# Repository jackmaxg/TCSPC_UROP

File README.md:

# TCSPC_UROP
Time Correlated Single Photon Counting Module

This is an open source project to develop a ~10 picosecond precision timing module, for time correlating pulses output by an avalanche photodiode quench circuit.

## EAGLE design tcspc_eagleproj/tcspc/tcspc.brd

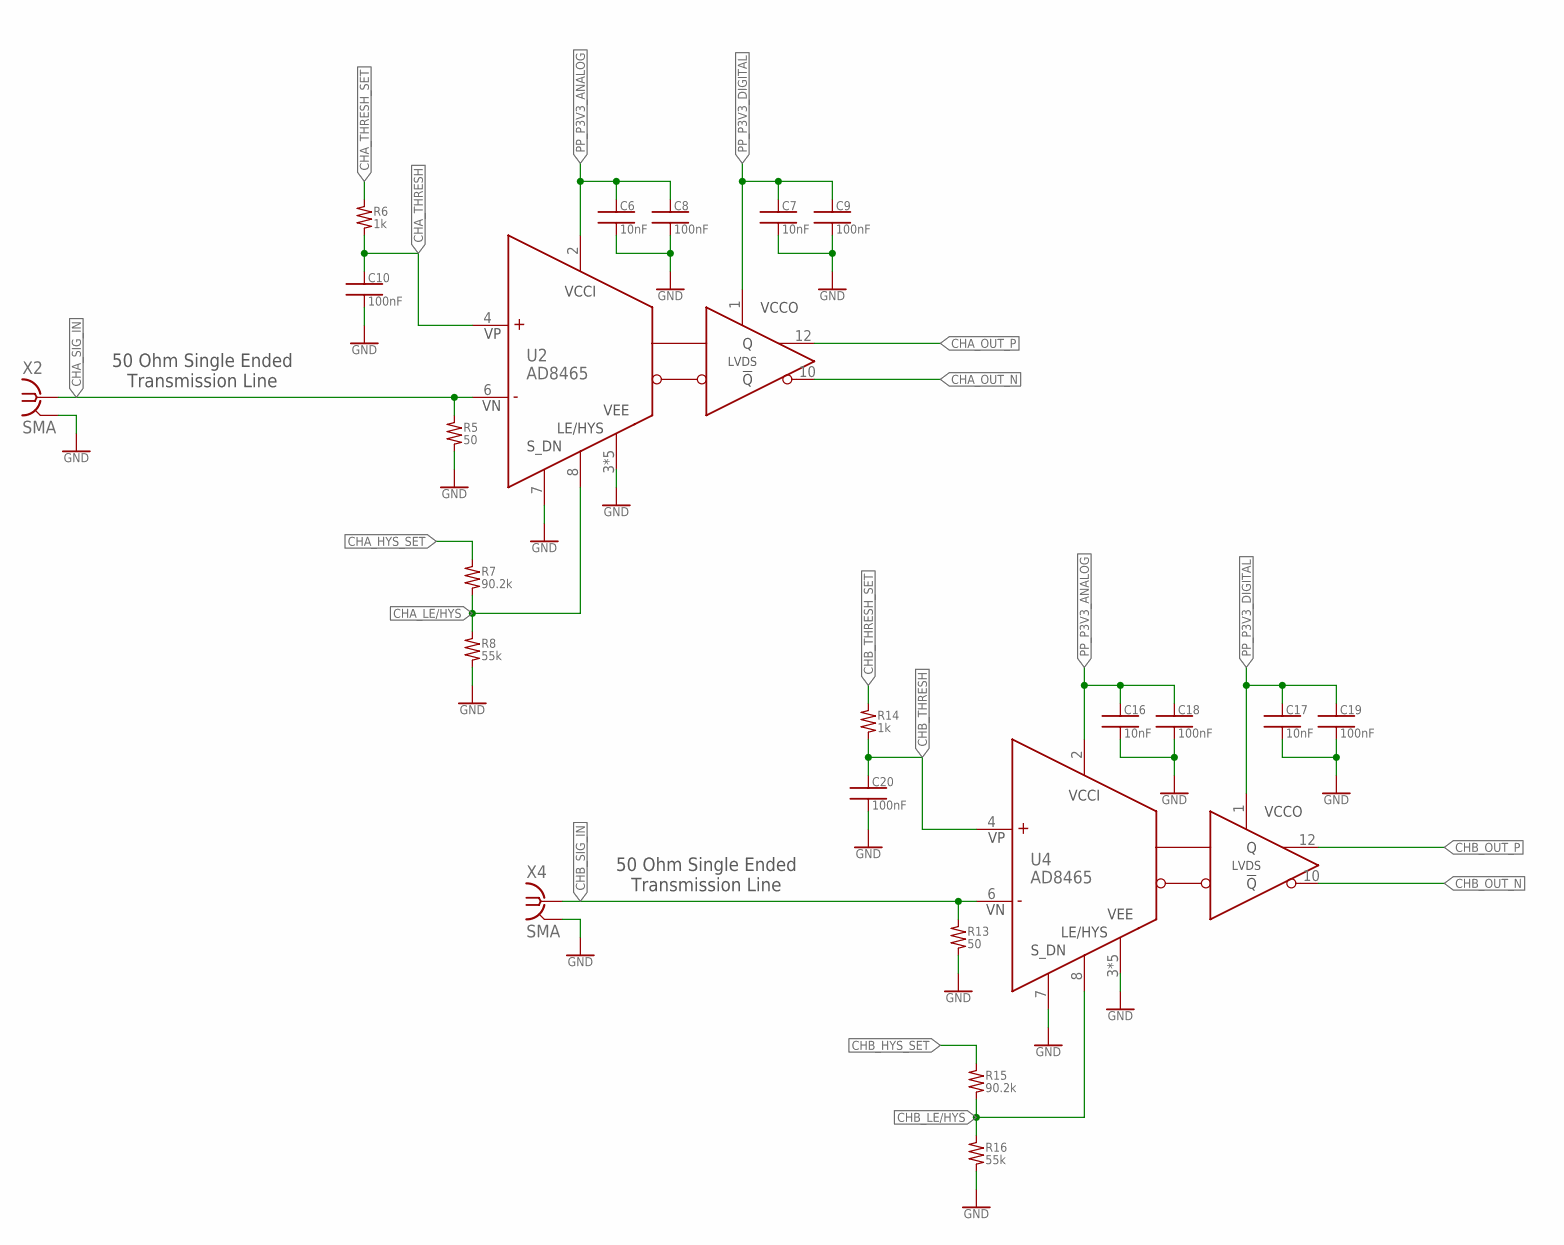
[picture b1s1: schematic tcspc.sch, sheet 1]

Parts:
C6, C7, C16, C17: 10nF; 0402
C8, C9, C10, C18, C19, C20: 100nF; 0402
R5, R13: 50; 0402
R6, R14: 1k; 0402
R7, R15: 90.2k; 0402
R8, R16: 55k; 0402
U2, U4: AD8465; LFCSP-12
X2, X4: SMA; J502-ND-142-0701-881/886

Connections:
CHA_HYS_SET: R7.1
CHA_LE/HYS: R7.2, R8.1, U2.8 (LE/HYS)
CHA_OUT_N: U2.10 (!Q)
CHA_OUT_P: U2.12 (Q)
CHA_SIG_IN: R5.1, U2.6 (VN), X2.1
CHA_THRESH: C10.1, R6.2, U2.4 (VP)
CHA_THRESH_SET: R6.1
CHB_HYS_SET: R15.1
CHB_LE/HYS: R15.2, R16.1, U4.8 (LE/HYS)
CHB_OUT_N: U4.10 (!Q)
CHB_OUT_P: U4.12 (Q)
CHB_SIG_IN: R13.1, U4.6 (VN), X4.1
CHB_THRESH: C20.1, R14.2, U4.4 (VP)
CHB_THRESH_SET: R14.1
GND: C6.2, C7.2, C8.2, C9.2, C10.2, C16.2, C17.2, C18.2, C19.2, C20.2, R5.2, R8.2, R13.2, R16.2, U2.3 (VEE), U2.5 (VEE), U2.7 (SDN), U2.9 (VEE), U2.11 (VEE), U2.EPAD (VEE), U4.3 (VEE), U4.5 (VEE), U4.7 (SDN), U4.9 (VEE), U4.11 (VEE), U4.EPAD (VEE), X2.G@1 (GND), X2.G@2 (GND), X2.G@3 (GND), X2.G@4 (GND), X4.G@1 (GND), X4.G@2 (GND), X4.G@3 (GND), X4.G@4 (GND); also elsewhere on the board
PP_P3V3_ANALOG: C6.1, C8.1, C16.1, C18.1, U2.2 (VCCI), U4.2 (VCCI); also elsewhere on the board
PP_P3V3_DIGITAL: C7.1, C9.1, C17.1, C19.1, U2.1 (VCCO), U4.1 (VCCO); also elsewhere on the board

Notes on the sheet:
50 Ohm Single Ended Transmission Line

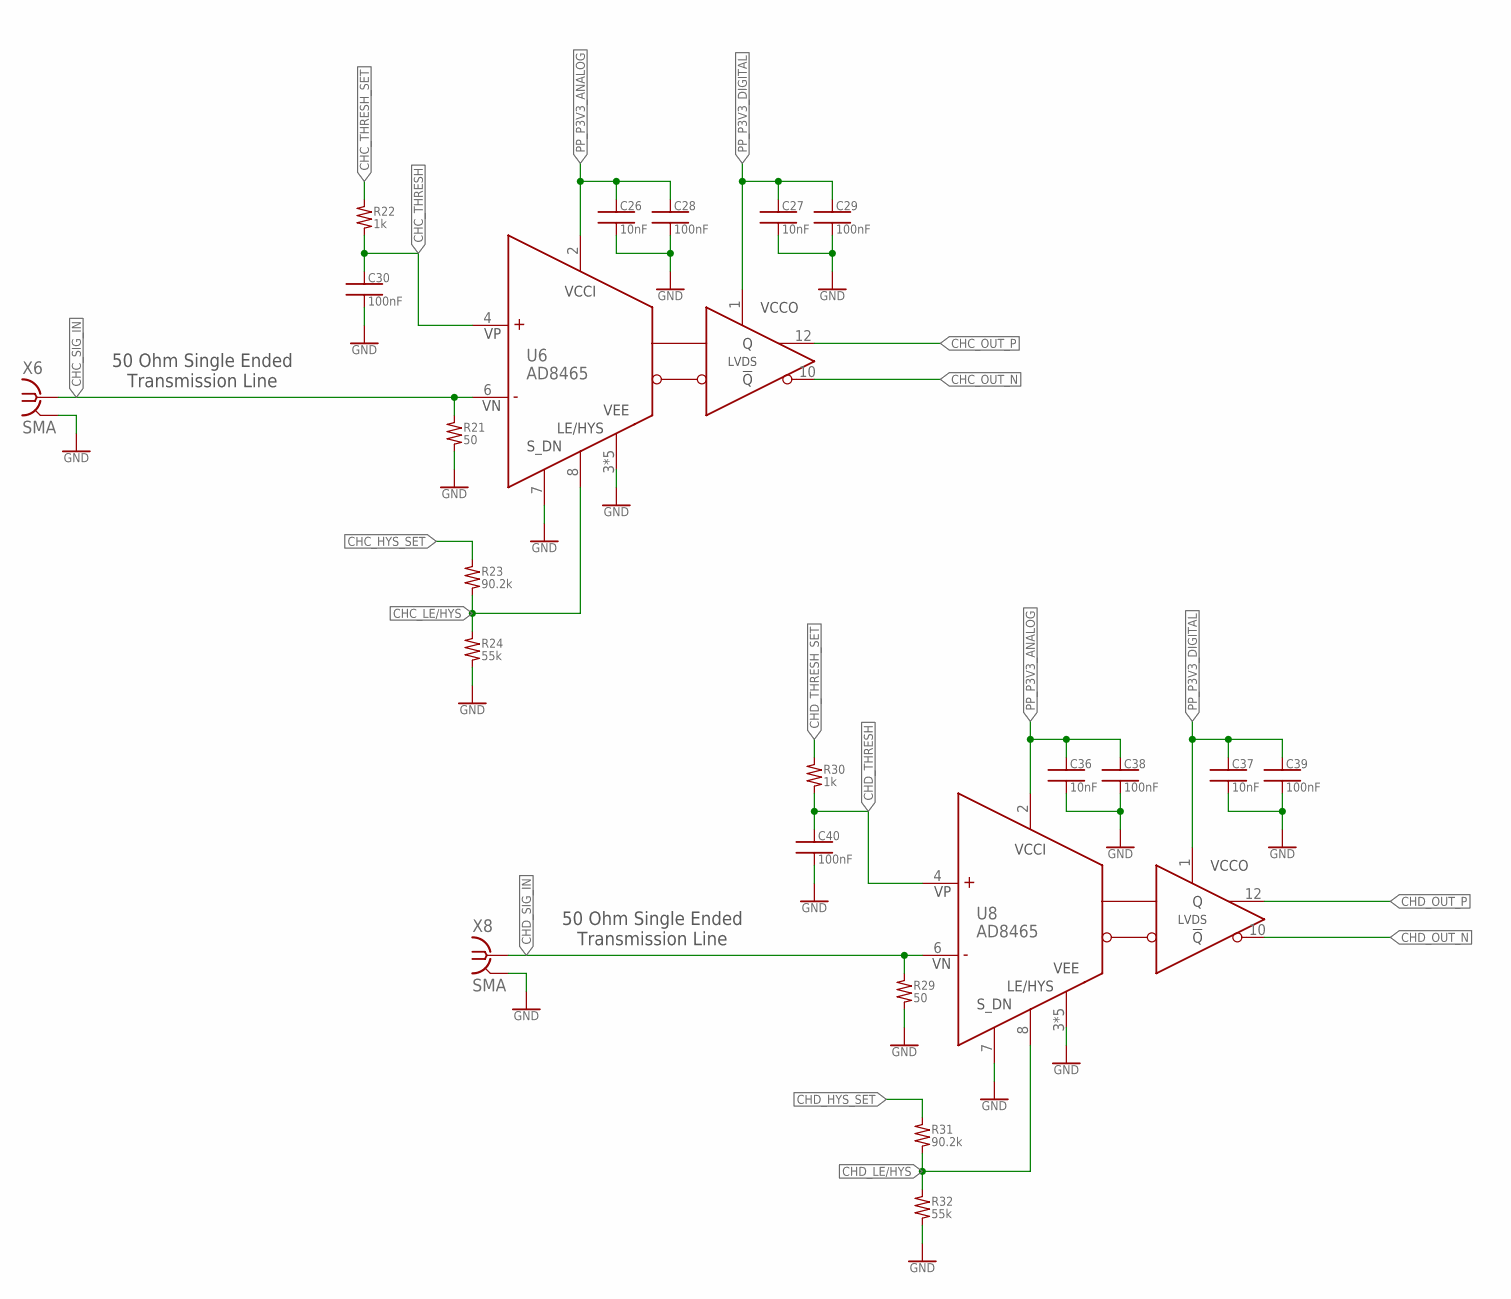
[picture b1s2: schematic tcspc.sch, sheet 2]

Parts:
C26, C27, C36, C37: 10nF; 0402
C28, C29, C30, C38, C39, C40: 100nF; 0402
R21, R29: 50; 0402
R22, R30: 1k; 0402
R23, R31: 90.2k; 0402
R24, R32: 55k; 0402
U6, U8: AD8465; LFCSP-12
X6, X8: SMA; J502-ND-142-0701-881/886

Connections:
CHC_HYS_SET: R23.1
CHC_LE/HYS: R23.2, R24.1, U6.8 (LE/HYS)
CHC_OUT_N: U6.10 (!Q)
CHC_OUT_P: U6.12 (Q)
CHC_SIG_IN: R21.1, U6.6 (VN), X6.1
CHC_THRESH: C30.1, R22.2, U6.4 (VP)
CHC_THRESH_SET: R22.1
CHD_HYS_SET: R31.1
CHD_LE/HYS: R31.2, R32.1, U8.8 (LE/HYS)
CHD_OUT_N: U8.10 (!Q)
CHD_OUT_P: U8.12 (Q)
CHD_SIG_IN: R29.1, U8.6 (VN), X8.1
CHD_THRESH: C40.1, R30.2, U8.4 (VP)
CHD_THRESH_SET: R30.1
GND: C26.2, C27.2, C28.2, C29.2, C30.2, C36.2, C37.2, C38.2, C39.2, C40.2, R21.2, R24.2, R29.2, R32.2, U6.3 (VEE), U6.5 (VEE), U6.7 (SDN), U6.9 (VEE), U6.11 (VEE), U6.EPAD (VEE), U8.3 (VEE), U8.5 (VEE), U8.7 (SDN), U8.9 (VEE), U8.11 (VEE), U8.EPAD (VEE), X6.G@1 (GND), X6.G@2 (GND), X6.G@3 (GND), X6.G@4 (GND), X8.G@1 (GND), X8.G@2 (GND), X8.G@3 (GND), X8.G@4 (GND); also elsewhere on the board
PP_P3V3_ANALOG: C26.1, C28.1, C36.1, C38.1, U6.2 (VCCI), U8.2 (VCCI); also elsewhere on the board
PP_P3V3_DIGITAL: C27.1, C29.1, C37.1, C39.1, U6.1 (VCCO), U8.1 (VCCO); also elsewhere on the board

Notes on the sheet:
50 Ohm Single Ended Transmission Line

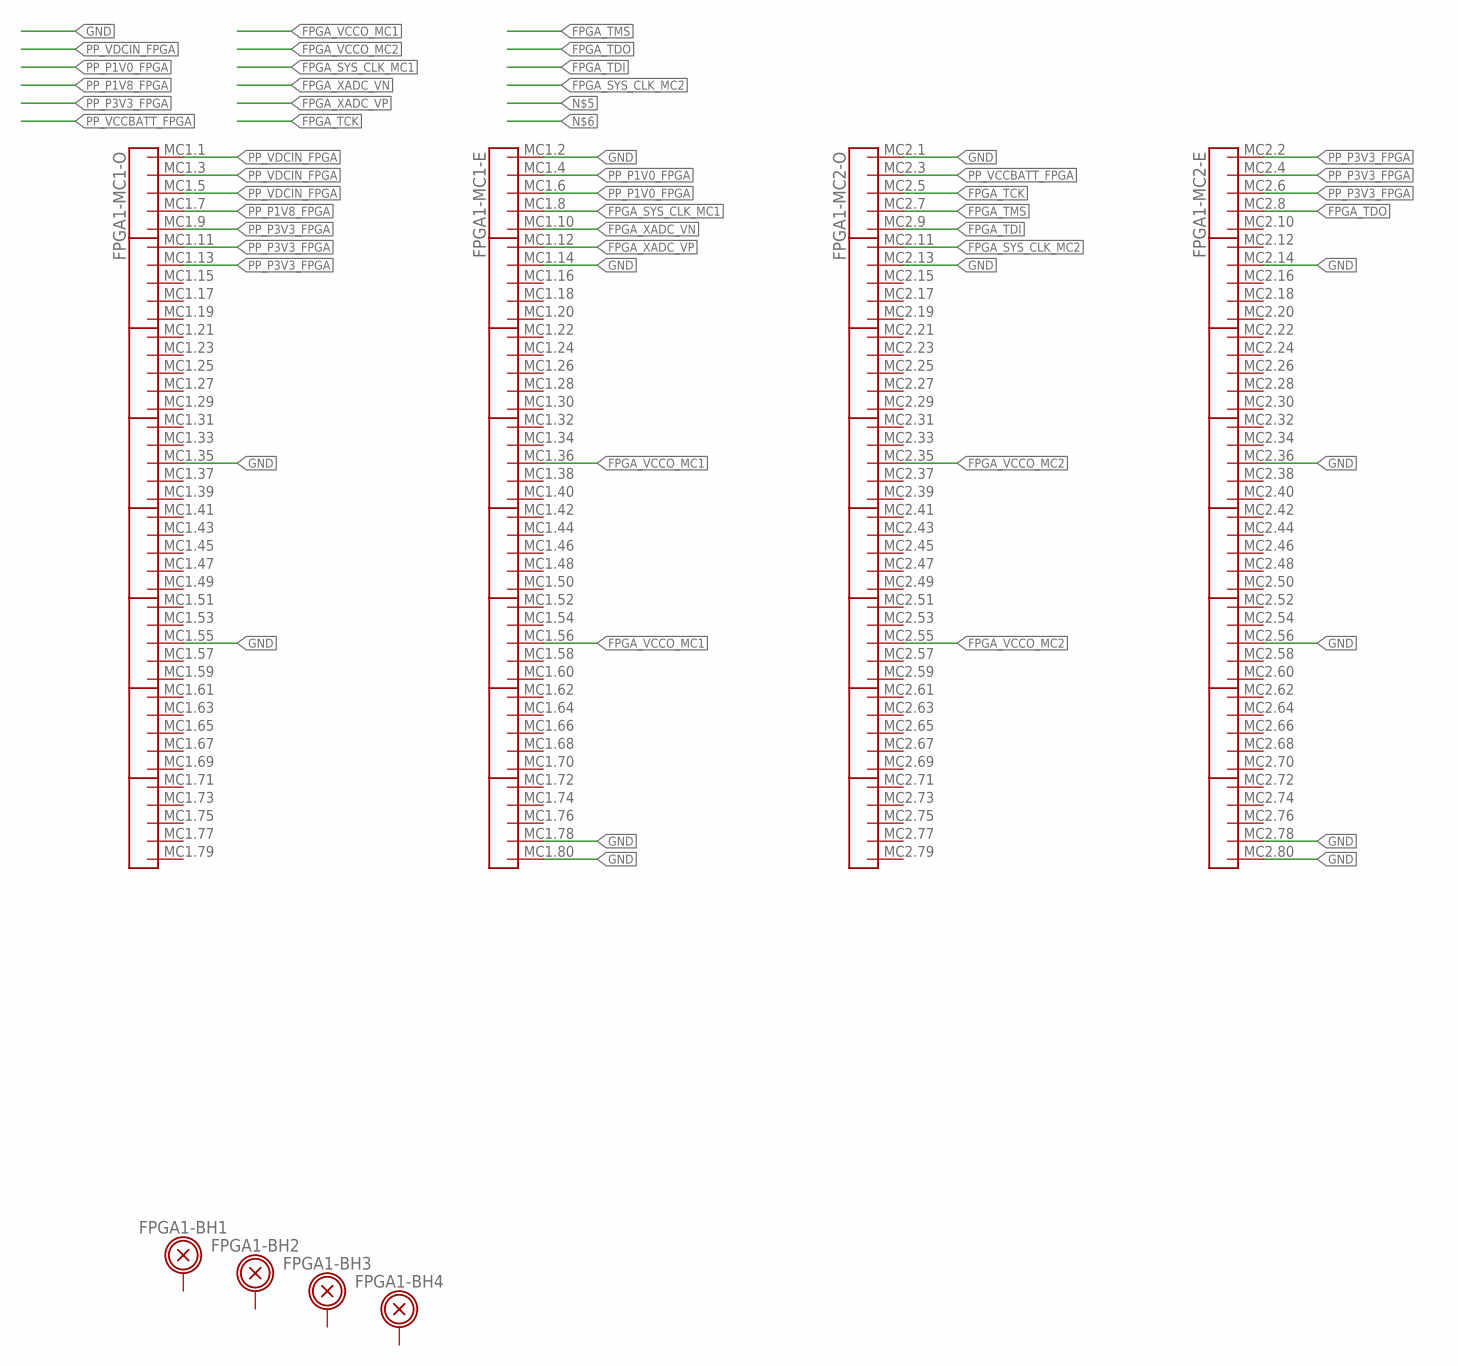
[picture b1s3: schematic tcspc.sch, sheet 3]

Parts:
FPGA1: XEM7310

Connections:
FPGA_SYS_CLK_MC1: FPGA1.MC1.8 (P4)
FPGA_SYS_CLK_MC2: FPGA1.MC2.11 (P6)
FPGA_TCK: FPGA1.MC2.5 (P3)
FPGA_TDI: FPGA1.MC2.9 (P5)
FPGA_TDO: FPGA1.MC2.8 (P4)
FPGA_TMS: FPGA1.MC2.7 (P4)
FPGA_VCCO_MC1: FPGA1.MC1.36 (P18), FPGA1.MC1.56 (P28)
FPGA_VCCO_MC2: FPGA1.MC2.35 (P18), FPGA1.MC2.55 (P28)
FPGA_XADC_VN: FPGA1.MC1.10 (P5)
FPGA_XADC_VP: FPGA1.MC1.12 (P6)
GND: FPGA1.MC1.2 (P1), FPGA1.MC1.14 (P7), FPGA1.MC1.35 (P18), FPGA1.MC1.55 (P28), FPGA1.MC1.78 (P39), FPGA1.MC1.80 (P40), FPGA1.MC2.1 (P1), FPGA1.MC2.13 (P7), FPGA1.MC2.14 (P7), FPGA1.MC2.36 (P18), FPGA1.MC2.56 (P28), FPGA1.MC2.78 (P39), FPGA1.MC2.80 (P40); also elsewhere on the board
PP_P1V0_FPGA: FPGA1.MC1.4 (P2), FPGA1.MC1.6 (P3)
PP_P1V8_FPGA: FPGA1.MC1.7 (P4)
PP_P3V3_FPGA: FPGA1.MC1.9 (P5), FPGA1.MC1.11 (P6), FPGA1.MC1.13 (P7), FPGA1.MC2.2 (P1), FPGA1.MC2.4 (P2), FPGA1.MC2.6 (P3)
PP_VCCBATT_FPGA: FPGA1.MC2.3 (P2)
PP_VDCIN_FPGA: FPGA1.MC1.1 (P1), FPGA1.MC1.3 (P2), FPGA1.MC1.5 (P3)

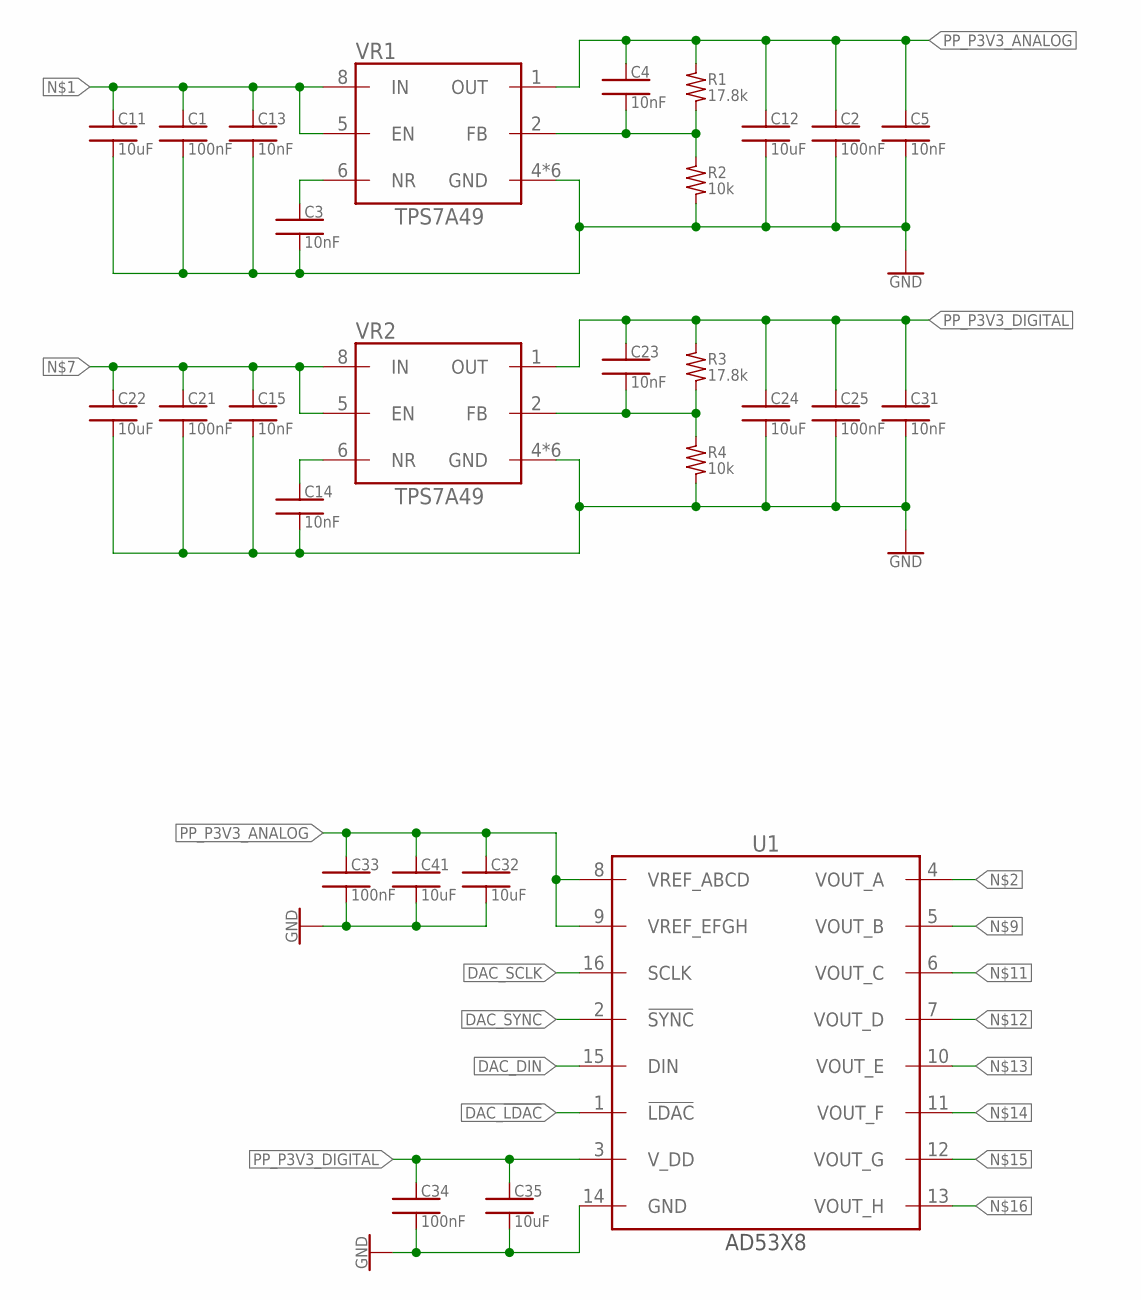
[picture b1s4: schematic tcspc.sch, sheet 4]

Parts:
C1, C2, C21, C25, C33, C34: 100nF; 0402
C3, C4, C5, C13, C14, C15, C23, C31: 10nF; 0402
C11, C12, C22, C24: 10uF; 0603
C32, C35, C41: 10uF; 0402
R1, R3: 17.8k; 0402
R2, R4: 10k; 0402
U1: AD53X8; TSSOP-16
VR1, VR2: TPS7A49; VSON

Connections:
DAC_!LDAC!: U1.1 (!LDAC)
DAC_!SYNC!: U1.2 (!SYNC)
DAC_DIN: U1.15 (DIN)
DAC_SCLK: U1.16 (SCLK)
GND: C1.2, C2.2, C3.2, C5.2, C11.2, C12.2, C13.2, C14.2, C15.2, C21.2, C22.2, C24.2, C25.2, C31.2, C32.2, C33.2, C34.2, C35.2, C41.2, R2.2, R4.2, U1.14 (GND), VR1.4 (GND), VR1.TP (GND), VR1.TP_A (GND), VR1.TP_B (GND), VR1.TP_C (GND), VR1.TP_D (GND), VR2.4 (GND), VR2.TP (GND), VR2.TP_A (GND), VR2.TP_B (GND), VR2.TP_C (GND), VR2.TP_D (GND); also elsewhere on the board
unnamed: C1.1, C11.1, C13.1, VR1.5 (EN), VR1.8 (IN)
unnamed: C4.2, R1.2, R2.1, VR1.2 (FB)
unnamed: C3.1, VR1.6 (NR)
unnamed: C15.1, C21.1, C22.1, VR2.5 (EN), VR2.8 (IN)
unnamed: C14.1, VR2.6 (NR)
unnamed: C23.2, R3.2, R4.1, VR2.2 (FB)
PP_P3V3_ANALOG: C2.1, C4.1, C5.1, C12.1, C32.1, C33.1, C41.1, R1.1, U1.8 (VREF_ABCD), U1.9 (VREF_EFGH), VR1.1 (OUT); also elsewhere on the board
PP_P3V3_DIGITAL: C23.1, C24.1, C25.1, C31.1, C34.1, C35.1, R3.1, U1.3 (V_DD), VR2.1 (OUT); also elsewhere on the board

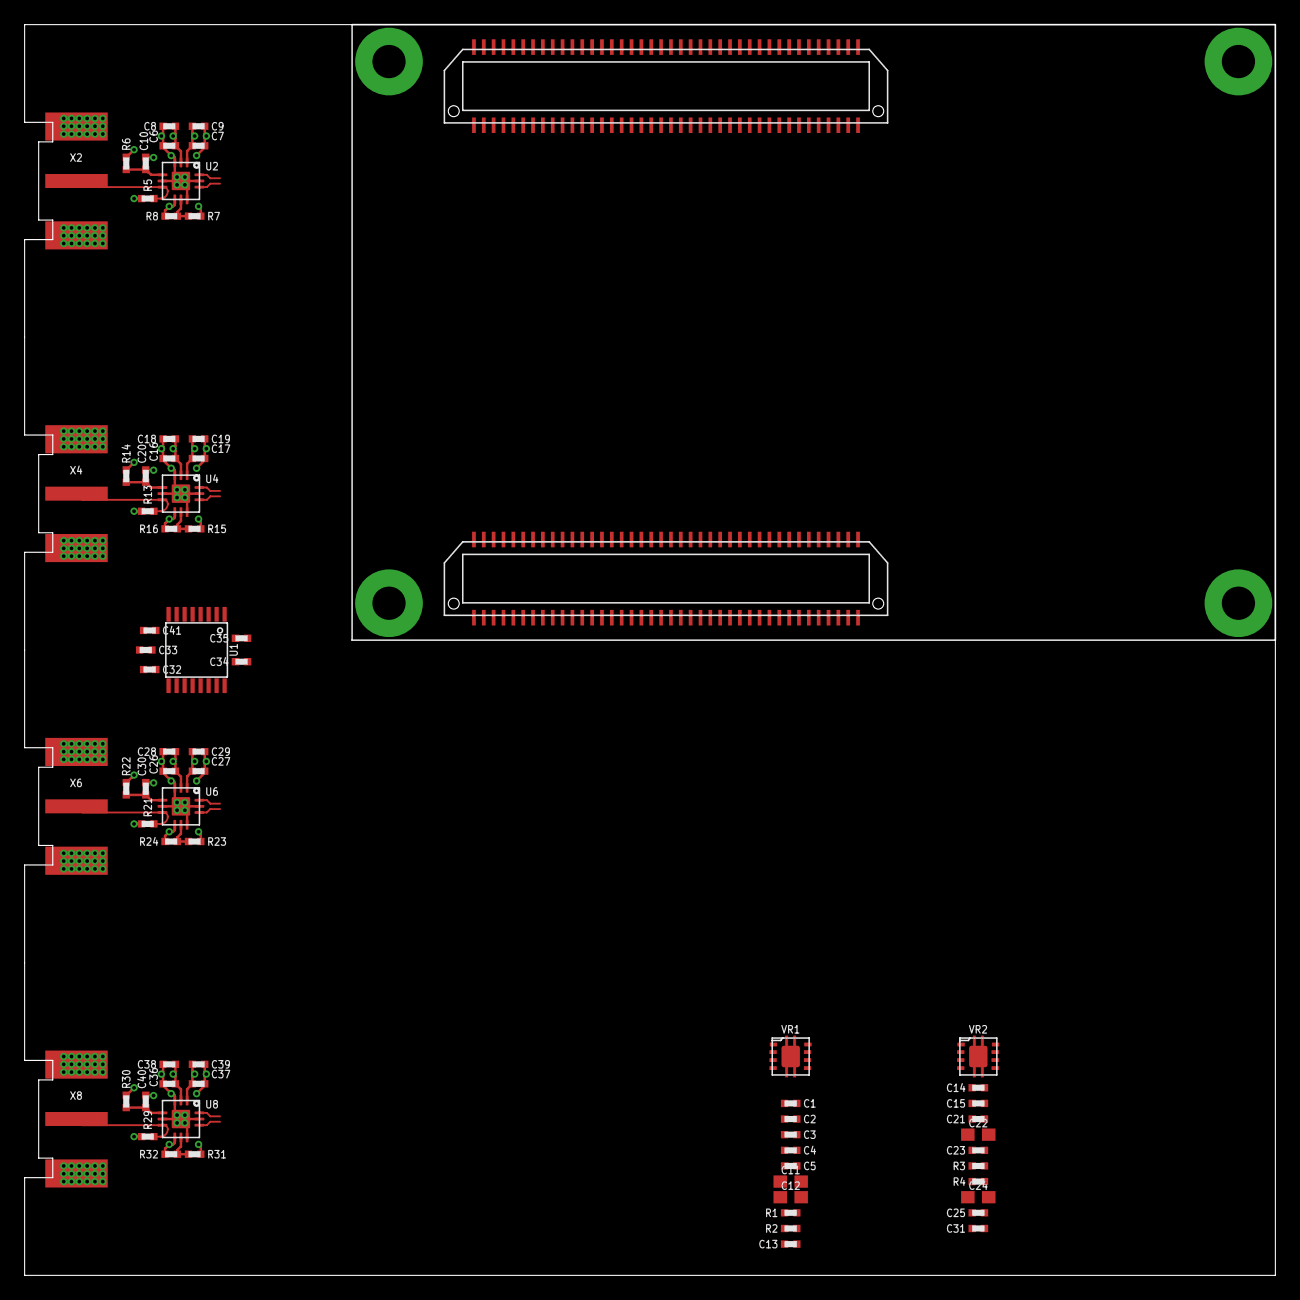
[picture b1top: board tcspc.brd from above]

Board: 4 copper layers, 101.6 x 101.6 mm, 73 parts (0 on the bottom side), 26 nets.

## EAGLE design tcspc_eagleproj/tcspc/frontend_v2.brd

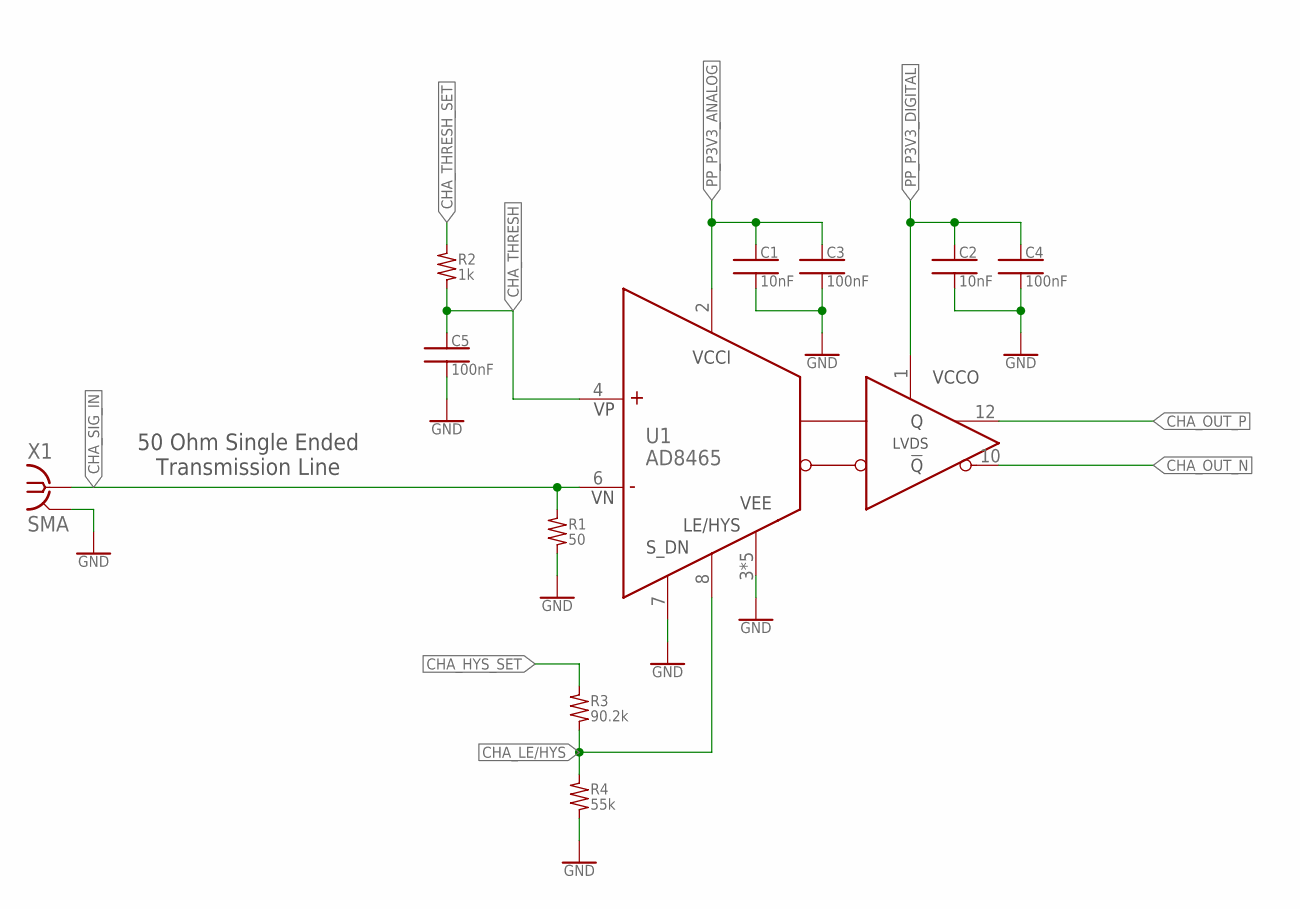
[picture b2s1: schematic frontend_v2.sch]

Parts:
C1, C2: 10nF; 0402
C3, C4, C5: 100nF; 0402
R1: 50; 0402
R2: 1k; 0402
R3: 90.2k; 0402
R4: 55k; 0402
U1: AD8465; LFCSP-12
X1: SMA; J502-ND-142-0701-881/886

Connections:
CHA_HYS_SET: R3.1
CHA_LE/HYS: R3.2, R4.1, U1.8 (LE/HYS)
CHA_OUT_N: U1.10 (!Q)
CHA_OUT_P: U1.12 (Q)
CHA_SIG_IN: R1.1, U1.6 (VN), X1.1
CHA_THRESH: C5.1, R2.2, U1.4 (VP)
CHA_THRESH_SET: R2.1
GND: C1.2, C2.2, C3.2, C4.2, C5.2, R1.2, R4.2, U1.3 (VEE), U1.5 (VEE), U1.7 (SDN), U1.9 (VEE), U1.11 (VEE), U1.EPAD (VEE), X1.G@1 (GND), X1.G@2 (GND), X1.G@3 (GND), X1.G@4 (GND)
PP_P3V3_ANALOG: C1.1, C3.1, U1.2 (VCCI)
PP_P3V3_DIGITAL: C2.1, C4.1, U1.1 (VCCO)

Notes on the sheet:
50 Ohm Single Ended Transmission Line

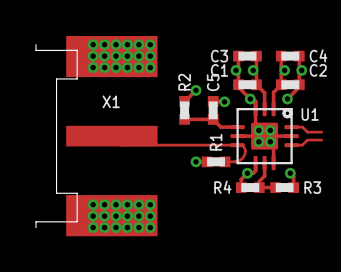
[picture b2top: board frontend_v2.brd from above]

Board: 4 copper layers, 11 parts (0 on the bottom side), 6 nets.

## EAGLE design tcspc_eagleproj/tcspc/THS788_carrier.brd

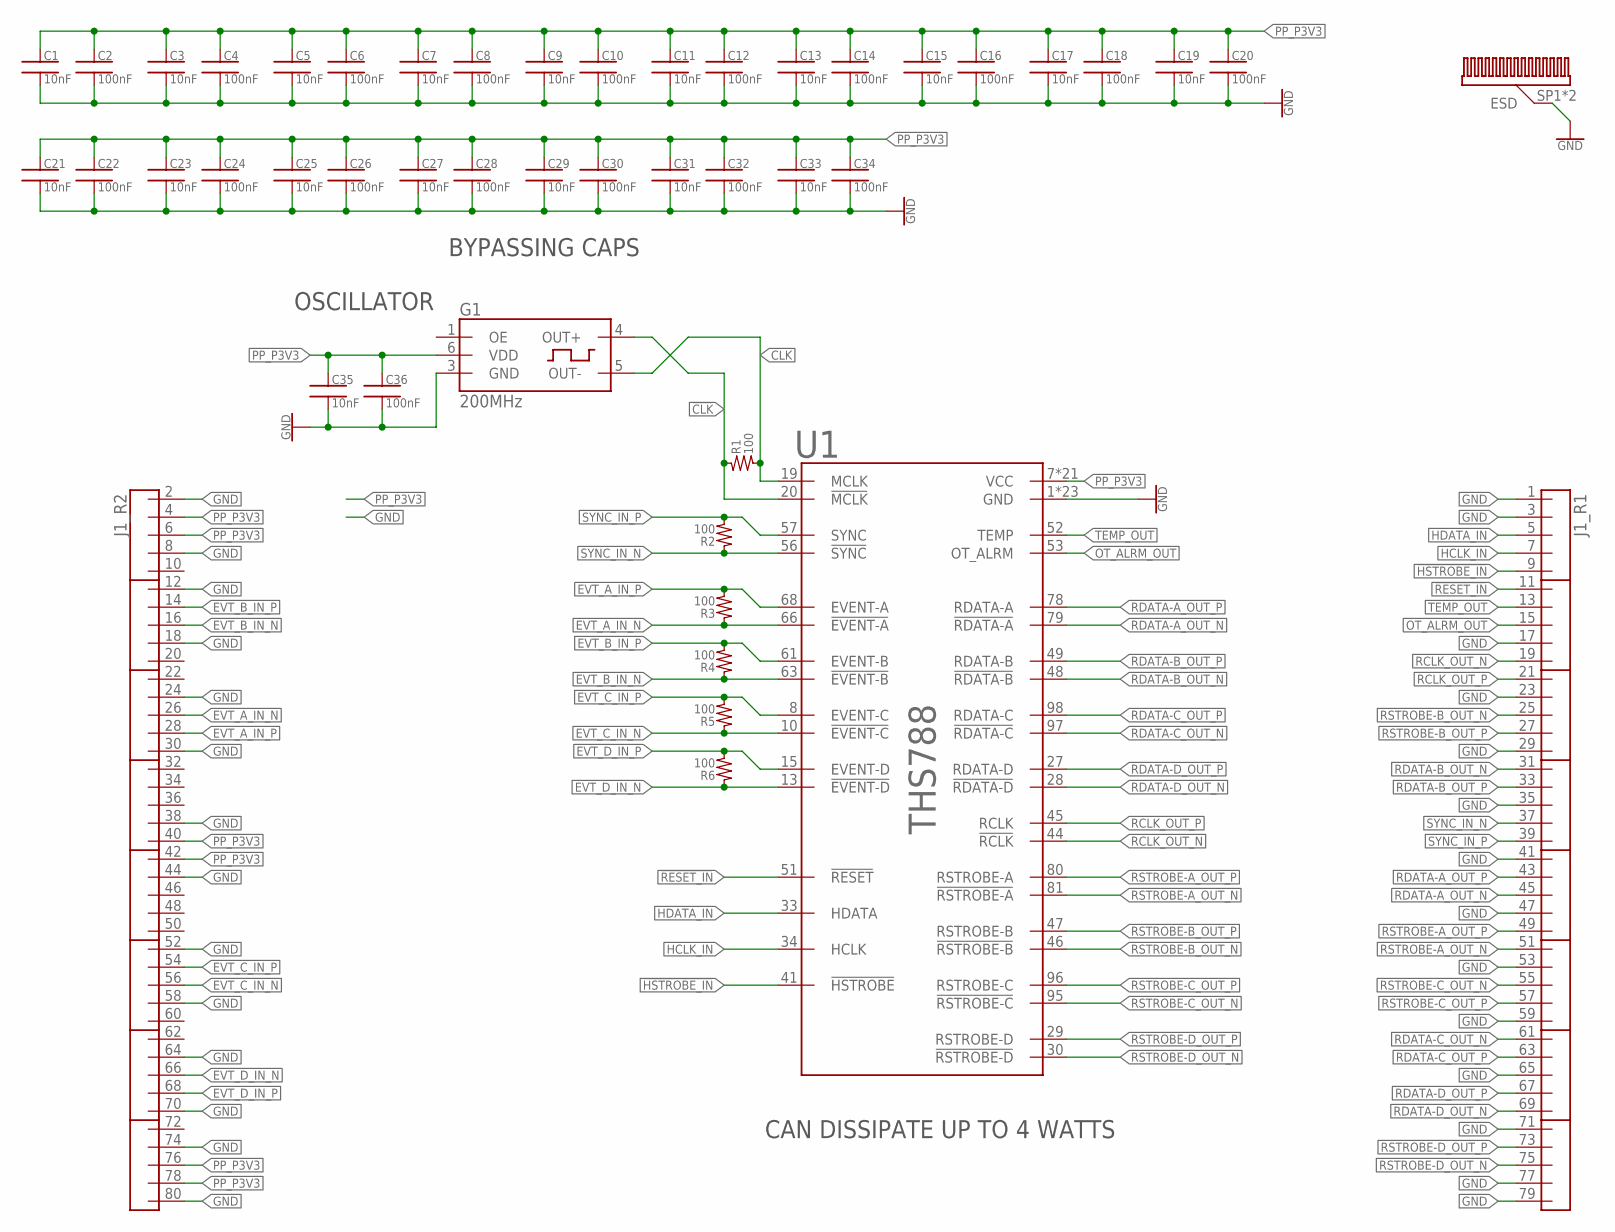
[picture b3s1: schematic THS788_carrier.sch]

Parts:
C1, C3, C5, C7, C9, C11, C13, C15, C17, C19, C21, C23, C25, C27, C29, C31, C33, C35: 10nF; 0402
C2, C4, C6, C8, C10, C12, C14, C16, C18, C20, C22, C24, C26, C28, C30, C32, C34, C36: 100nF; 0402
G1: 200MHz; SIT5021_5X3.2
HTSINK1: ATS_HEATSINK; ATS-FPX025025010-43-C2-R0
J1: BXE-040-01-F-D-A_BSE; BSE-040-01-F-D-A
R1, R2, R3, R4, R5, R6: 100; 0402
U1: THS788; S-QFP-G100

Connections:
!CLK!: G1.4 (OUT+), R1.1, U1.20 (!MCLK)
!HSTROBE_IN: J1.9 (P5), U1.41 (!HSTROBE)
!RESET_IN: J1.11 (P6), U1.51 (!RESET)
CLK: G1.5 (OUT-), R1.2, U1.19 (MCLK)
EVT_A_IN_N: J1.26 (P13), R3.1, U1.66 (!EVENT-A)
EVT_A_IN_P: J1.28 (P14), R3.2, U1.68 (EVENT-A)
EVT_B_IN_N: J1.16 (P8), R4.1, U1.63 (!EVENT-B)
EVT_B_IN_P: J1.14 (P7), R4.2, U1.61 (EVENT-B)
EVT_C_IN_N: J1.56 (P28), R5.1, U1.10 (!EVENT-C)
EVT_C_IN_P: J1.54 (P27), R5.2, U1.8 (EVENT-C)
EVT_D_IN_N: J1.66 (P33), R6.1, U1.13 (!EVENT-D)
EVT_D_IN_P: J1.68 (P34), R6.2, U1.15 (EVENT-D)
GND: C1.2, C2.2, C3.2, C4.2, C5.2, C6.2, C7.2, C8.2, C9.2, C10.2, C11.2, C12.2, C13.2, C14.2, C15.2, C16.2, C17.2, C18.2, C19.2, C20.2, C21.2, C22.2, C23.2, C24.2, C25.2, C26.2, C27.2, C28.2, C29.2, C30.2, C31.2, C32.2, C33.2, C34.2, C35.2, C36.2, G1.3 (GND), HTSINK1.SP1, HTSINK1.SP2, J1.1, J1.2 (P1), J1.3 (P2), J1.8 (P4), J1.12 (P6), J1.17 (P9), J1.18 (P9), J1.23 (P12), J1.24 (P12), J1.29 (P15), J1.30 (P15), J1.35 (P18), J1.38 (P19), J1.41 (P21), J1.44 (P22), J1.47 (P24), J1.52 (P26), J1.53 (P27), J1.58 (P29), J1.59 (P30), J1.64 (P32), J1.65 (P33), J1.70 (P35), J1.71 (P36), J1.74 (P37), J1.77 (P39), J1.79 (P40), J1.80 (P40), U1.1 (GND), U1.2 (GND), U1.11 (GND), U1.12 (GND), U1.21 (GND), U1.25 (GND), U1.32 (GND), U1.35 (GND), U1.37 (GND), U1.39 (GND), U1.42 (GND), U1.55 (GND), U1.64 (GND), U1.65 (GND), U1.74 (GND), U1.75 (GND), U1.82 (GND), U1.84 (GND), U1.85 (GND), U1.87 (GND), U1.89 (GND), U1.92 (GND), U1.94 (GND)
HCLK_IN: J1.7 (P4), U1.34 (HCLK)
HDATA_IN: J1.5 (P3), U1.33 (HDATA)
OT_ALRM_OUT: J1.15 (P8), U1.53 (OT_ALRM)
PP_P3V3: C1.1, C2.1, C3.1, C4.1, C5.1, C6.1, C7.1, C8.1, C9.1, C10.1, C11.1, C12.1, C13.1, C14.1, C15.1, C16.1, C17.1, C18.1, C19.1, C20.1, C21.1, C22.1, C23.1, C24.1, C25.1, C26.1, C27.1, C28.1, C29.1, C30.1, C31.1, C32.1, C33.1, C34.1, C35.1, C36.1, G1.6 (VDD), J1.4 (P2), J1.6 (P3), J1.40 (P20), J1.42 (P21), J1.76 (P38), J1.78 (P39), U1.7 (VCC), U1.16 (VCC), U1.22 (VCC), U1.23 (VCC), U1.24 (VCC), U1.31 (VCC), U1.36 (VCC), U1.38 (VCC), U1.40 (VCC), U1.43 (VCC), U1.58 (VCC), U1.60 (VCC), U1.69 (VCC), U1.77 (VCC), U1.83 (VCC), U1.86 (VCC), U1.88 (VCC), U1.90 (VCC), U1.91 (VCC), U1.93 (VCC), U1.99 (VCC)
RCLK_OUT_N: J1.19 (P10), U1.44 (!RCLK)
RCLK_OUT_P: J1.21 (P11), U1.45 (RCLK)
RDATA-A_OUT_N: J1.45 (P23), U1.79 (!RDATA-A)
RDATA-A_OUT_P: J1.43 (P22), U1.78 (RDATA-A)
RDATA-B_OUT_N: J1.31 (P16), U1.48 (!RDATA-B)
RDATA-B_OUT_P: J1.33 (P17), U1.49 (RDATA-B)
RDATA-C_OUT_N: J1.61 (P31), U1.97 (!RDATA-C)
RDATA-C_OUT_P: J1.63 (P32), U1.98 (RDATA-C)
RDATA-D_OUT_N: J1.69 (P35), U1.28 (!RDATA-D)
RDATA-D_OUT_P: J1.67 (P34), U1.27 (RDATA-D)
RSTROBE-A_OUT_N: J1.51 (P26), U1.81 (!RSTROBE-A)
RSTROBE-A_OUT_P: J1.49 (P25), U1.80 (RSTROBE-A)
RSTROBE-B_OUT_N: J1.25 (P13), U1.46 (!RSTROBE-B)
RSTROBE-B_OUT_P: J1.27 (P14), U1.47 (RSTROBE-B)
RSTROBE-C_OUT_N: J1.55 (P28), U1.95 (!RSTROBE-C)
RSTROBE-C_OUT_P: J1.57 (P29), U1.96 (RSTROBE-C)
RSTROBE-D_OUT_N: J1.75 (P38), U1.30 (!RSTROBE-D)
RSTROBE-D_OUT_P: J1.73 (P37), U1.29 (RSTROBE-D)
SYNC_IN_N: J1.37 (P19), R2.1, U1.56 (!SYNC)
SYNC_IN_P: J1.39 (P20), R2.2, U1.57 (SYNC)
TEMP_OUT: J1.13 (P7), U1.52 (TEMP)

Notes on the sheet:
BYPASSING CAPS
OSCILLATOR
CAN DISSIPATE UP TO 4 WATTS

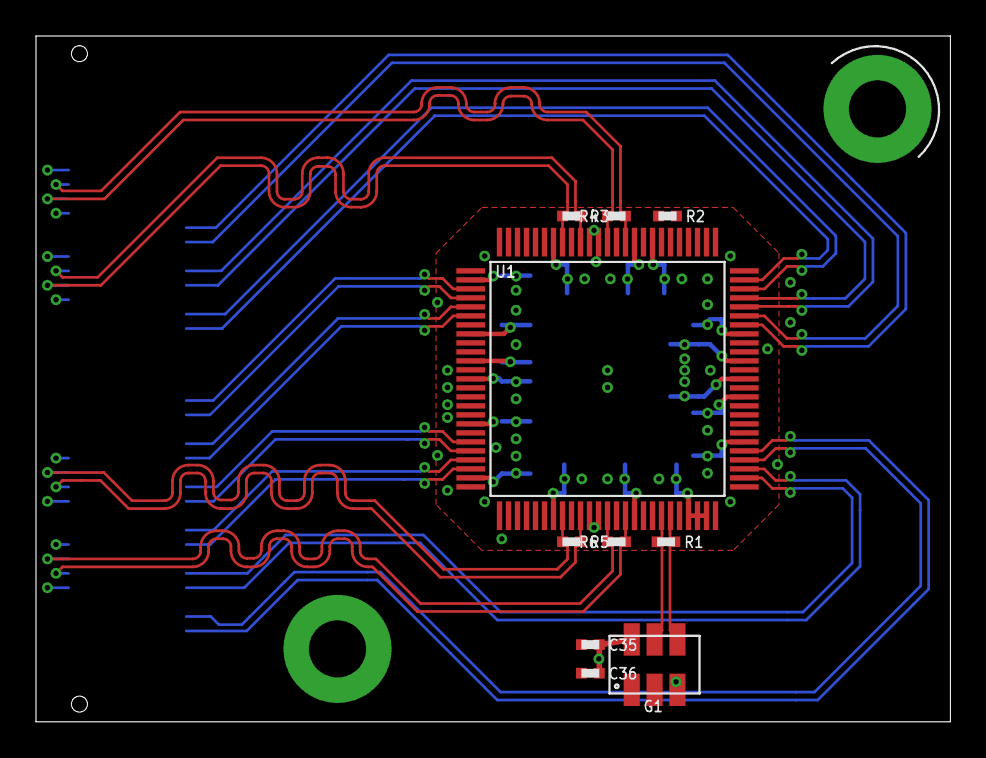
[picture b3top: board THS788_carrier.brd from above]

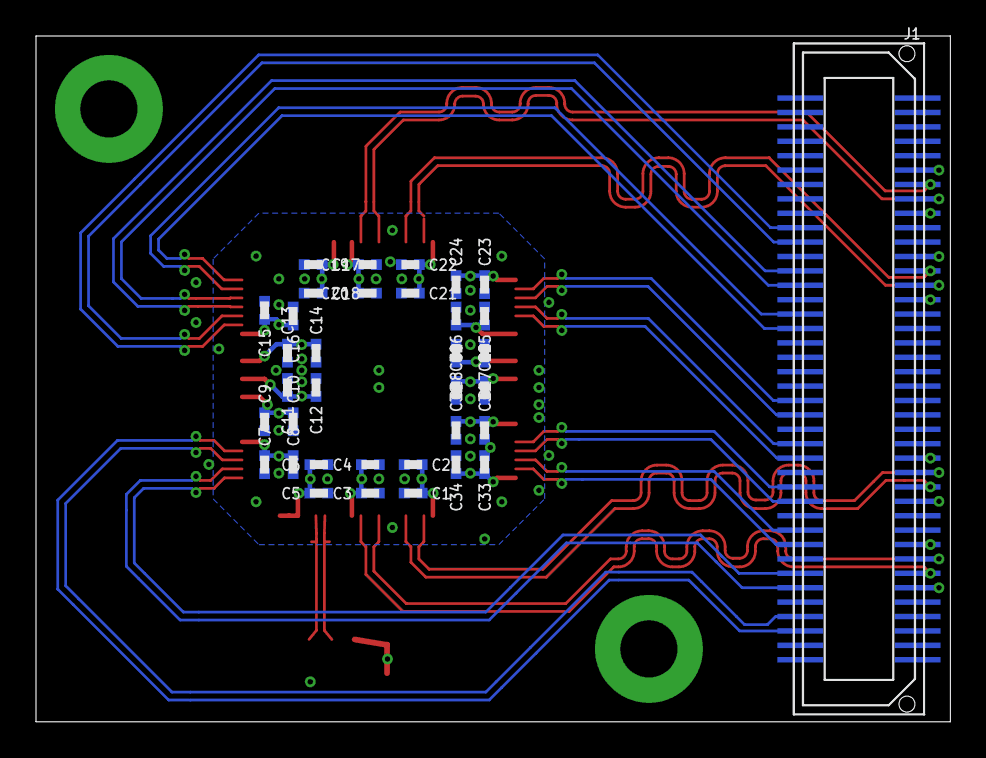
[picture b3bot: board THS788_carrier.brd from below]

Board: 4 copper layers, 50.8 x 38.1 mm, 46 parts (35 on the bottom side), 38 nets.
